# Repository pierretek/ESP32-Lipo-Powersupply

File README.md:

# 3.7V Lipo Charger to 3.3V Power Supply 

A 3.7V LiPo battery charging circuit coupled with a buck-boost converter to provide steady **3.3V** for an **ESP32**

**View the [interactive BOM](https://pierretek.github.io/ESP32-Lipo-Powersupply/) here!**
 
## Features 
- Battery under-voltage and over-voltage protection **(2.800V - 4.275V)**
- Built-in buck-boost converter to provide a steady 3.3V to the ESP32
- A pair of 1*15 pin headers compatible with a `30-pin ESP32 Devkit V1` 
- `USB-C` port for charging, and `2.54mm JST-XH` connector for battery
- Can charge the lipo battery at **~485mA** while providing **~500mA** to the ESP32

> [!NOTE]
> To keep the ESP32’s pins accessible, use [stacking headers](https://www.aliexpress.com/item/1005008090018820.html) so the board can plug into a breadboard or another module underneath.

## Important Files
- KiCad project: `/kicad`
- JLCPCB production files: `/production_files`
- Gerbers: `/gerber`
  
## Key IC's
- **[BQ24070RHLR](https://jlcpcb.com/partdetail/TexasInstruments-BQ24070RHLR/C6514)** - main charging IC + power path management
  - [datasheet](https://www.lcsc.com/datasheet/C6514.pdf)
- **[BQ29700DSER](https://jlcpcb.com/partdetail/TexasInstruments-BQ29700DSER/C183096)** - battery protection IC
  - [datasheet](https://www.lcsc.com/datasheet/C183096.pdf)
- **[FS8205A](https://jlcpcb.com/partdetail/FUXINSEMI-FS8205A/C908265)** - dual mosfet
  - [datasheet](https://www.lcsc.com/datasheet/C908265.pdf)
- **[TPS63001DRCR](https://jlcpcb.com/partdetail/TexasInstruments-TPS63001DRCR/C28060)** - 3.3V buck-boost converter
  - [datasheet](https://www.lcsc.com/datasheet/C28060.pdf)

## Image Gallery
### Schematic (i know its messy)

### PCB top view 

### 3D view

## Credits / Tools Used
- KiCad 
- [kicad-jlcpcb-tools](https://github.com/bouni/kicad-jlcpcb-tools) (to generate the jlcpcb files)
- [InteractiveHtmlBom](https://github.com/openscopeproject/interactivehtmlbom) (for the [interactive html BOM](https://pierretek.github.io/ESP32-Lipo-Powersupply/))

_thanks for reading_

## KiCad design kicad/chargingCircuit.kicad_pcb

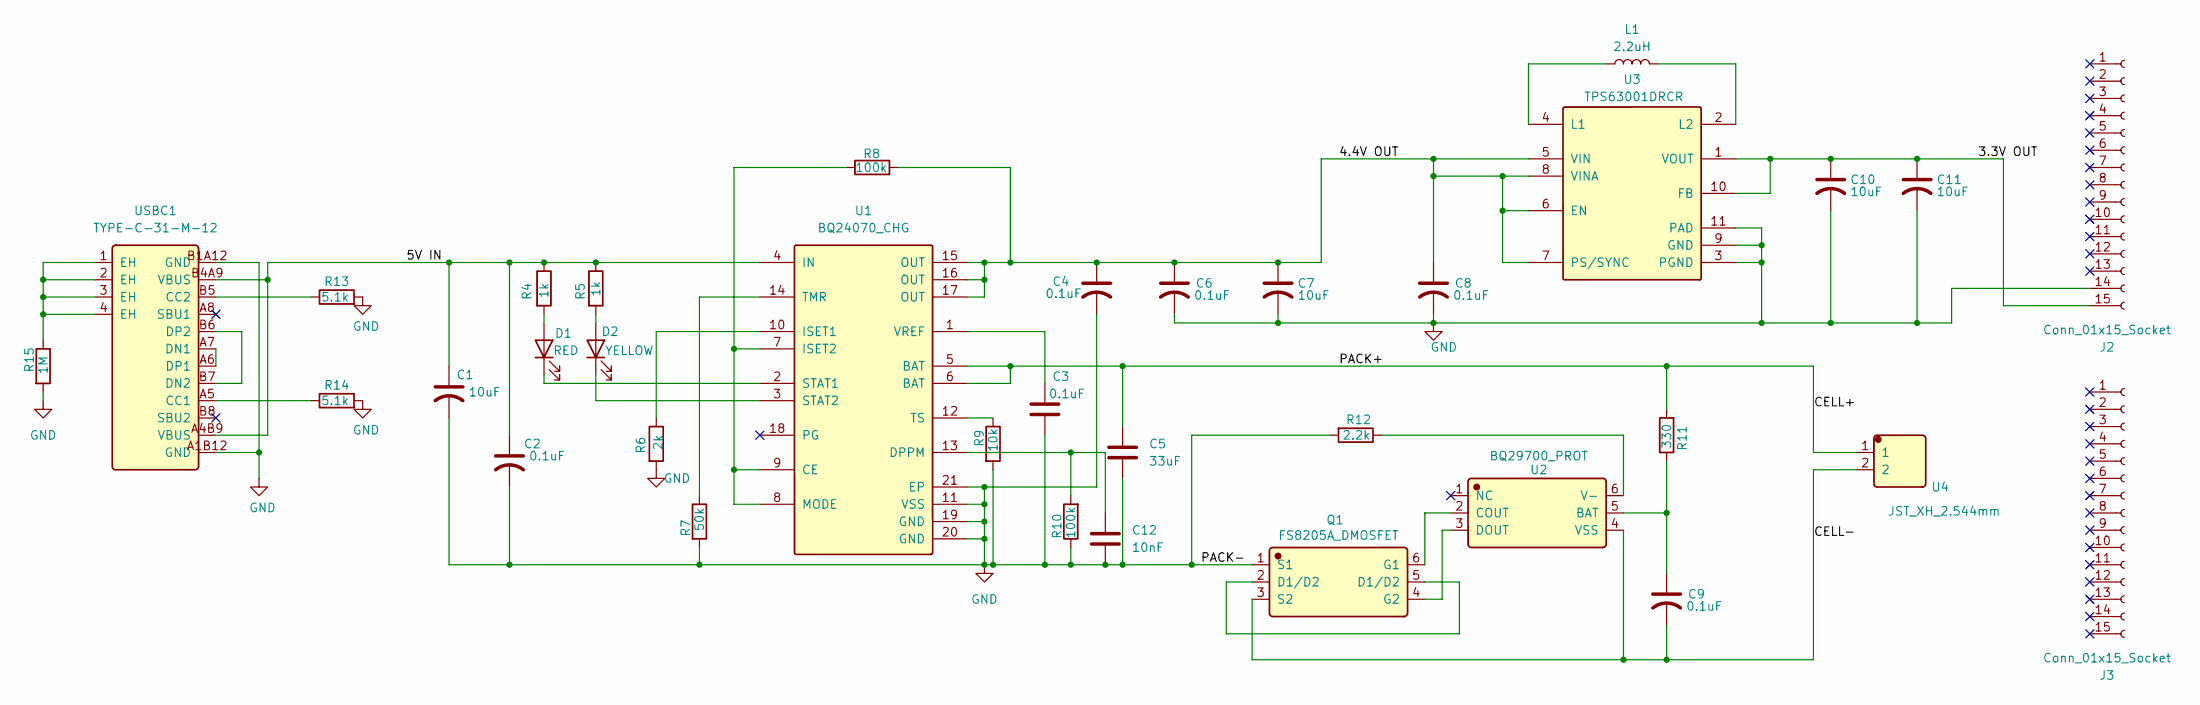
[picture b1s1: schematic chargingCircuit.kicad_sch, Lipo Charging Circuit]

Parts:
C1, C7, C10, C11: 10uF; C_0402_1005Metric; LCSC C15525
C2, C3, C4, C6, C8, C9: 0.1uF; C_0402_1005Metric; LCSC C1525
C5: 33uF; C_0805_2012Metric; LCSC C342307
C12: 10nF; C_0402_1005Metric; LCSC C15195
D1: RED; LED_0805_2012Metric; LCSC C2286
D2: YELLOW; LED_0805_2012Metric; LCSC C2290
J2, J3: Conn_01x15_Socket; PinSocket_1x15_P2.54mm_Vertical
L1: 2.2uH; L_0603_1608Metric; LCSC C6079477
Q1: FS8205A_DMOSFET; FS8205A_C908265; Manufacturer Part FS8205A; LCSC C908265
R4, R5: 1k; R_0402_1005Metric; LCSC C11702
R6: 2k; R_0402_1005Metric; LCSC C4109
R7: 50k; R_0603_1608Metric; LCSC C23184
R8, R10: 100k; R_0402_1005Metric; LCSC C25741
R9: 10k; R_0402_1005Metric; LCSC C25744
R11: 330; R_0402_1005Metric; LCSC C25104
R12: 2.2k; R_0402_1005Metric; LCSC C25879
R13, R14: 5.1k; R_0402_1005Metric; LCSC C25905
R15: 1M; R_0402_1005Metric; LCSC C26083
U1: BQ24070_CHG; BQ24070RHLR; Manufacturer Part BQ24070RHLR; LCSC C6514
U2: BQ29700_PROT; BQ29700DSER; Manufacturer Part BQ29700DSER; LCSC C183096
U3: TPS63001DRCR; Manufacturer Part TPS63001DRCR; LCSC C28060
U4: JST_XH_2.544mm; S2B-XH-A-_LF_SN; Manufacturer Part S2B-XH-A(LF)(SN); LCSC C157931
USBC1: TYPE-C-31-M-12; Manufacturer Part TYPE-C-31-M-12; LCSC C165948

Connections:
/3.3V OUT: C10.1, C11.1, J2.15, U3.1 (VOUT), U3.10 (FB)
/4.4V OUT: C4.1, C6.1, C7.1, C8.1, R8.2, U1.15 (OUT), U1.16 (OUT), U1.17 (OUT), U3.5 (VIN), U3.6 (EN), U3.7 (PS/SYNC), U3.8 (VINA)
/5V IN: C1.1, C2.1, R4.1, R5.1, U1.4 (IN), USBC1.A4B9 (VBUS), USBC1.B4A9 (VBUS)
/CELL+: C5.1, R11.2, U1.5 (BAT), U1.6 (BAT), U4.1
/CELL-: C9.2, Q1.3 (S2), U2.4 (VSS), U4.2
GND: C1.2, C2.2, C3.2, C4.2, C5.2, C6.2, C7.2, C8.2, C10.2, C11.2, C12.2, J2.14, Q1.1 (S1), R6.2, R7.2, R9.2, R10.1, R12.2, R13.2, R14.2, R15.2, U1.11 (VSS), U1.19 (GND), U1.20 (GND), U1.21 (EP), U3.3 (PGND), U3.9 (GND), U3.11 (PAD), USBC1.A1B12 (GND), USBC1.B1A12 (GND)
unnamed: D1.2 (A), R4.2
unnamed: D1.1 (K), U1.2 (STAT1)
unnamed: D2.2 (A), R5.2
unnamed: D2.1 (K), U1.3 (STAT2)
unnamed: Q1.2 (D1/D2), Q1.5 (D1/D2)
unnamed: Q1.6 (G1), U2.2 (COUT)
unnamed: Q1.4 (G2), U2.3 (DOUT)
unnamed: R15.1, USBC1.1 (EH), USBC1.2 (EH), USBC1.3 (EH), USBC1.4 (EH)
unnamed: R8.1, U1.7 (ISET2), U1.8 (MODE), U1.9 (CE)
unnamed: C12.1, R10.2, U1.13 (DPPM)
unnamed: R6.1, U1.10 (ISET1)
unnamed: R7.1, U1.14 (TMR)
unnamed: R9.1, U1.12 (TS)
unnamed: C3.1, U1.1 (VREF)
unnamed: C9.1, R11.1, U2.5 (BAT)
unnamed: R12.1, U2.6 (V-)
unnamed: L1.1, U3.4 (L1)
unnamed: L1.2, U3.2 (L2)
unnamed: R14.1, USBC1.A5 (CC1)
unnamed: R13.1, USBC1.B5 (CC2)
unnamed: USBC1.A6 (DP1), USBC1.A7 (DN1)
unnamed: USBC1.B6 (DP2), USBC1.B7 (DN2)

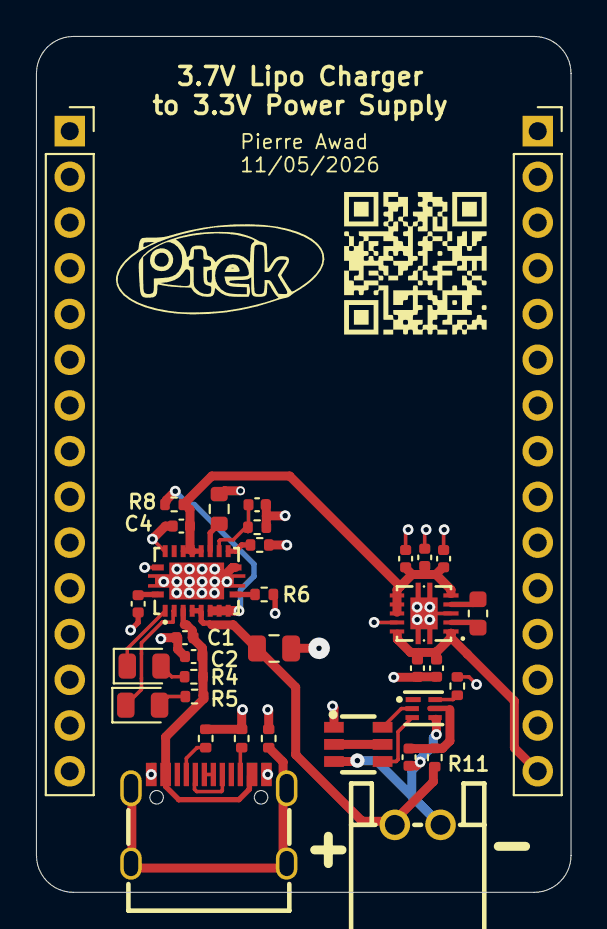
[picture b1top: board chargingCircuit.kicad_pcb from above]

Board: 2 copper layers, 29.7 x 47.5 mm, 35 parts (0 on the bottom side), 28 nets.

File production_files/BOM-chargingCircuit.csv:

Comment,Designator,Footprint,LCSC,Quantity
BQ24070_CHG,U1,BQ24070RHLR,C6514,1
BQ29700_PROT,U2,BQ29700DSER,C183096,1
FS8205A_DMOSFET,Q1,FS8205A_C908265,C908265,1
JST_XH_2.544mm,U4,S2B-XH-A-_LF_SN,C157931,1
TPS63001DRCR,U3,TPS63001DRCR,C28060,1
TYPE-C-31-M-12,USBC1,TYPE-C-31-M-12,C165948,1
10nF,C12,C_0402_1005Metric,,1
100k,R10,R_0402_1005Metric,,1
10uF,C11,C_0402_1005Metric,,1
0.1uF,C9,C_0402_1005Metric,,1
10uF,C10,C_0402_1005Metric,,1
YELLOW,D2,LED_0805_2012Metric,,1
0.1uF,C8,C_0402_1005Metric,,1
50k,R7,R_0603_1608Metric,,1
Conn_01x15_Socket,J2,PinSocket_1x15_P2.54mm_Vertical,,1
0.1uF,C3,C_0402_1005Metric,,1
2.2k,R12,R_0402_1005Metric,,1
2.2uH,L1,L_0603_1608Metric,,1
10uF,C1,C_0402_1005Metric,,1
1k,R5,R_0402_1005Metric,,1
5.1k,R14,R_0402_1005Metric,,1
10k,R9,R_0402_1005Metric,,1
2k,R6,R_0402_1005Metric,,1
0.1uF,C4,C_0402_1005Metric,,1
100k,R8,R_0402_1005Metric,,1
Conn_01x15_Socket,J3,PinSocket_1x15_P2.54mm_Vertical,,1
330,R11,R_0402_1005Metric,,1
RED,D1,LED_0805_2012Metric,,1
5.1k,R13,R_0402_1005Metric,,1
0.1uF,C2,C_0402_1005Metric,,1
33uF,C5,C_0805_2012Metric,,1
1M,R15,R_0402_1005Metric,,1
10uF,C7,C_0402_1005Metric,,1
0.1uF,C6,C_0402_1005Metric,,1
1k,R4,R_0402_1005Metric,,1

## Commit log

2026-05-13 fixing the links in README
2026-05-20 added kicad project files and added charging information to README
